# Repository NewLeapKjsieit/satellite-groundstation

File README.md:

# satellite-groundstation

Includes a arduino program to control ground station rotators

Componets->

1. esp8266 ( controller + wifi)	
	https://www.espressif.com/sites/default/files/documentation/0a-esp8266ex_datasheet_en.pdf
	-provide unregulted power supply to it
	-

2. drv8825 x 2(motor controller)-----
	https://www.pololu.com/product/2133
	https://lastminuteengineers.com/drv8825-stepper-motor-driver-arduino-tutorial/

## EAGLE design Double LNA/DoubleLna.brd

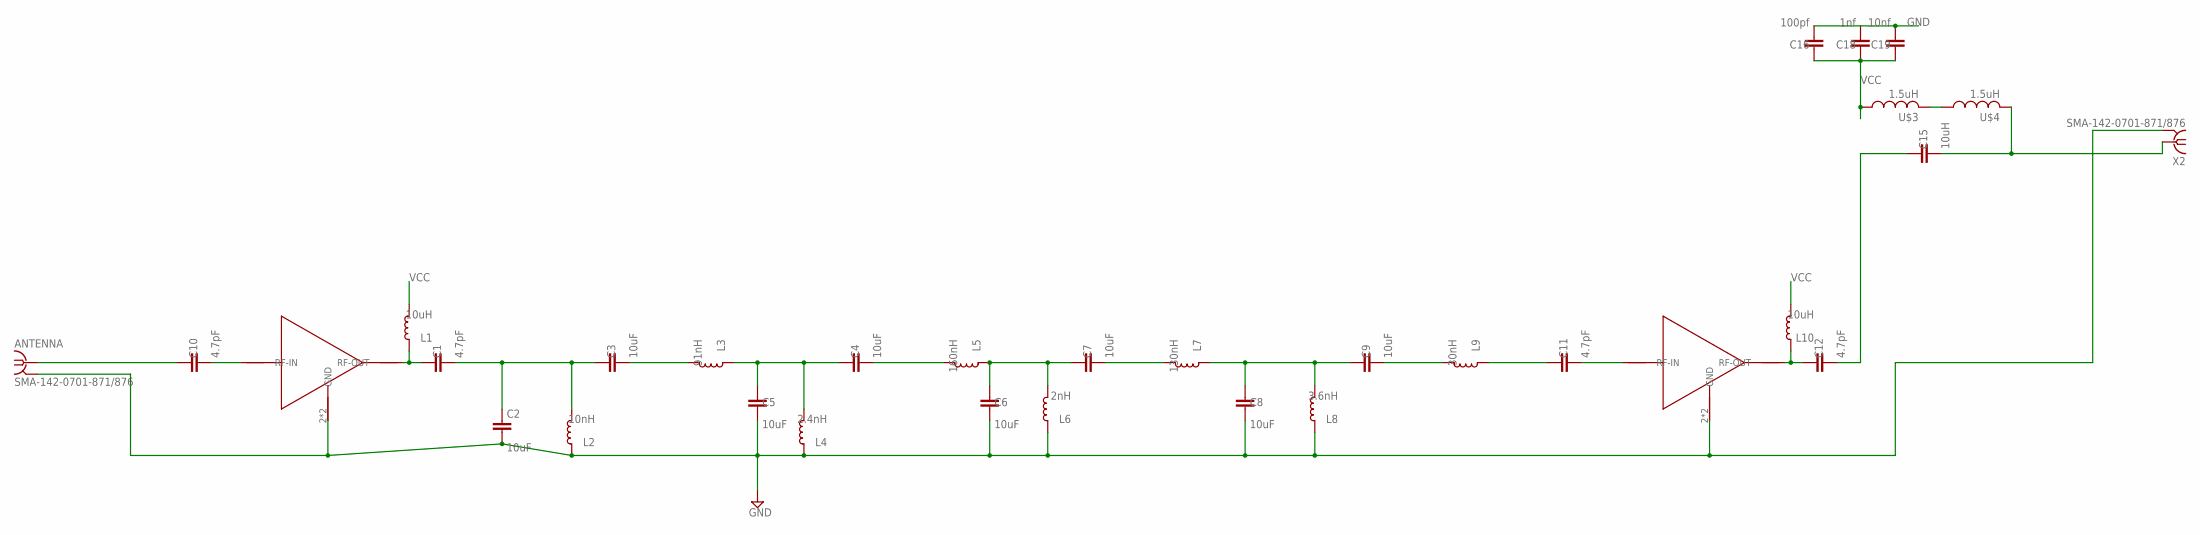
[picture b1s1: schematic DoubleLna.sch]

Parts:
ANTENNA: SMA-142-0701-871/876; J502-ND-142-0701-871/876
C1, C10, C11, C12: 4.7pF; 0603
C2, C3, C4, C5, C6, C7, C8, C9: 10uF; 0603
C15: 10uH; 0603
C16: 100pf; 0603
C18: 1nf; 0603
C19: 10nf; 0603
L1, L10: 10uH; L0603
L2: 10nH; L0603
L3: 91nH; L0603
L4: 2.4nH; L0603
L5: 160nH; L0603
L6: 2nH; L0603
L7: 130nH; L0603
L8: 3.6nH; L0603
L9: 30nH; L0603
U$1, U$2: PSA4-5043+
U$3, U$4: 1.5uH; C0504
X2: SMA-142-0701-871/876; J502-ND-142-0701-871/876

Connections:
GND: ANTENNA.G@1 (2), ANTENNA.G@2 (2), ANTENNA.G@3 (2), ANTENNA.G@4 (2), C2.2, C5.2, C6.2, C8.2, C16.2, C18.2, C19.2, L2.2, L4.2, L6.2, L8.2, U$1.2 (GND), U$1.4 (GND), U$2.2 (GND), U$2.4 (GND), X2.G@1 (2), X2.G@2 (2), X2.G@3 (2), X2.G@4 (2)
unnamed: ANTENNA.1, C10.1
unnamed: C1.2, C2.1, C3.1, L2.1
unnamed: C3.2, L3.1
unnamed: C4.1, C5.1, L3.2, L4.1
unnamed: C4.2, L5.1
unnamed: C6.1, C7.1, L5.2, L6.1
unnamed: C7.2, L7.1
unnamed: C8.1, C9.1, L7.2, L8.1
unnamed: C9.2, L9.1
unnamed: C10.2, U$1.3 (RF-IN)
unnamed: C1.1, L1.2, U$1.1 (RF-OUT)
unnamed: C12.1, L10.2, U$2.1 (RF-OUT)
unnamed: C11.2, U$2.3 (RF-IN)
unnamed: C12.2, C15.1
unnamed: C11.1, L9.2
unnamed: C15.2, U$4.2, X2.1
unnamed: U$3.2, U$4.1
VCC: C16.1, C18.1, C19.1, L1.1, L10.1, U$3.1

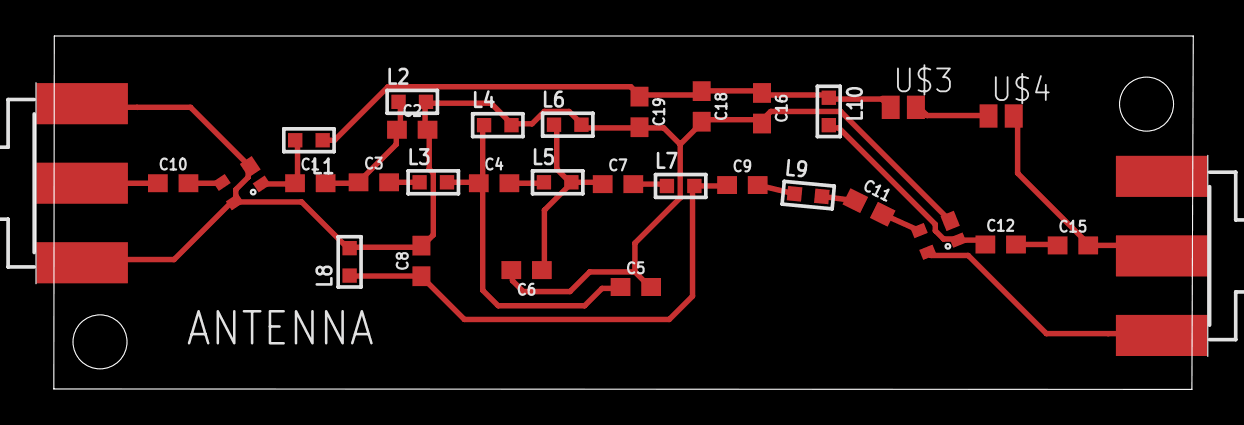
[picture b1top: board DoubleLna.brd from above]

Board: 2 copper layers, 65.1 x 19.6 mm, 32 parts (0 on the bottom side), 19 nets.

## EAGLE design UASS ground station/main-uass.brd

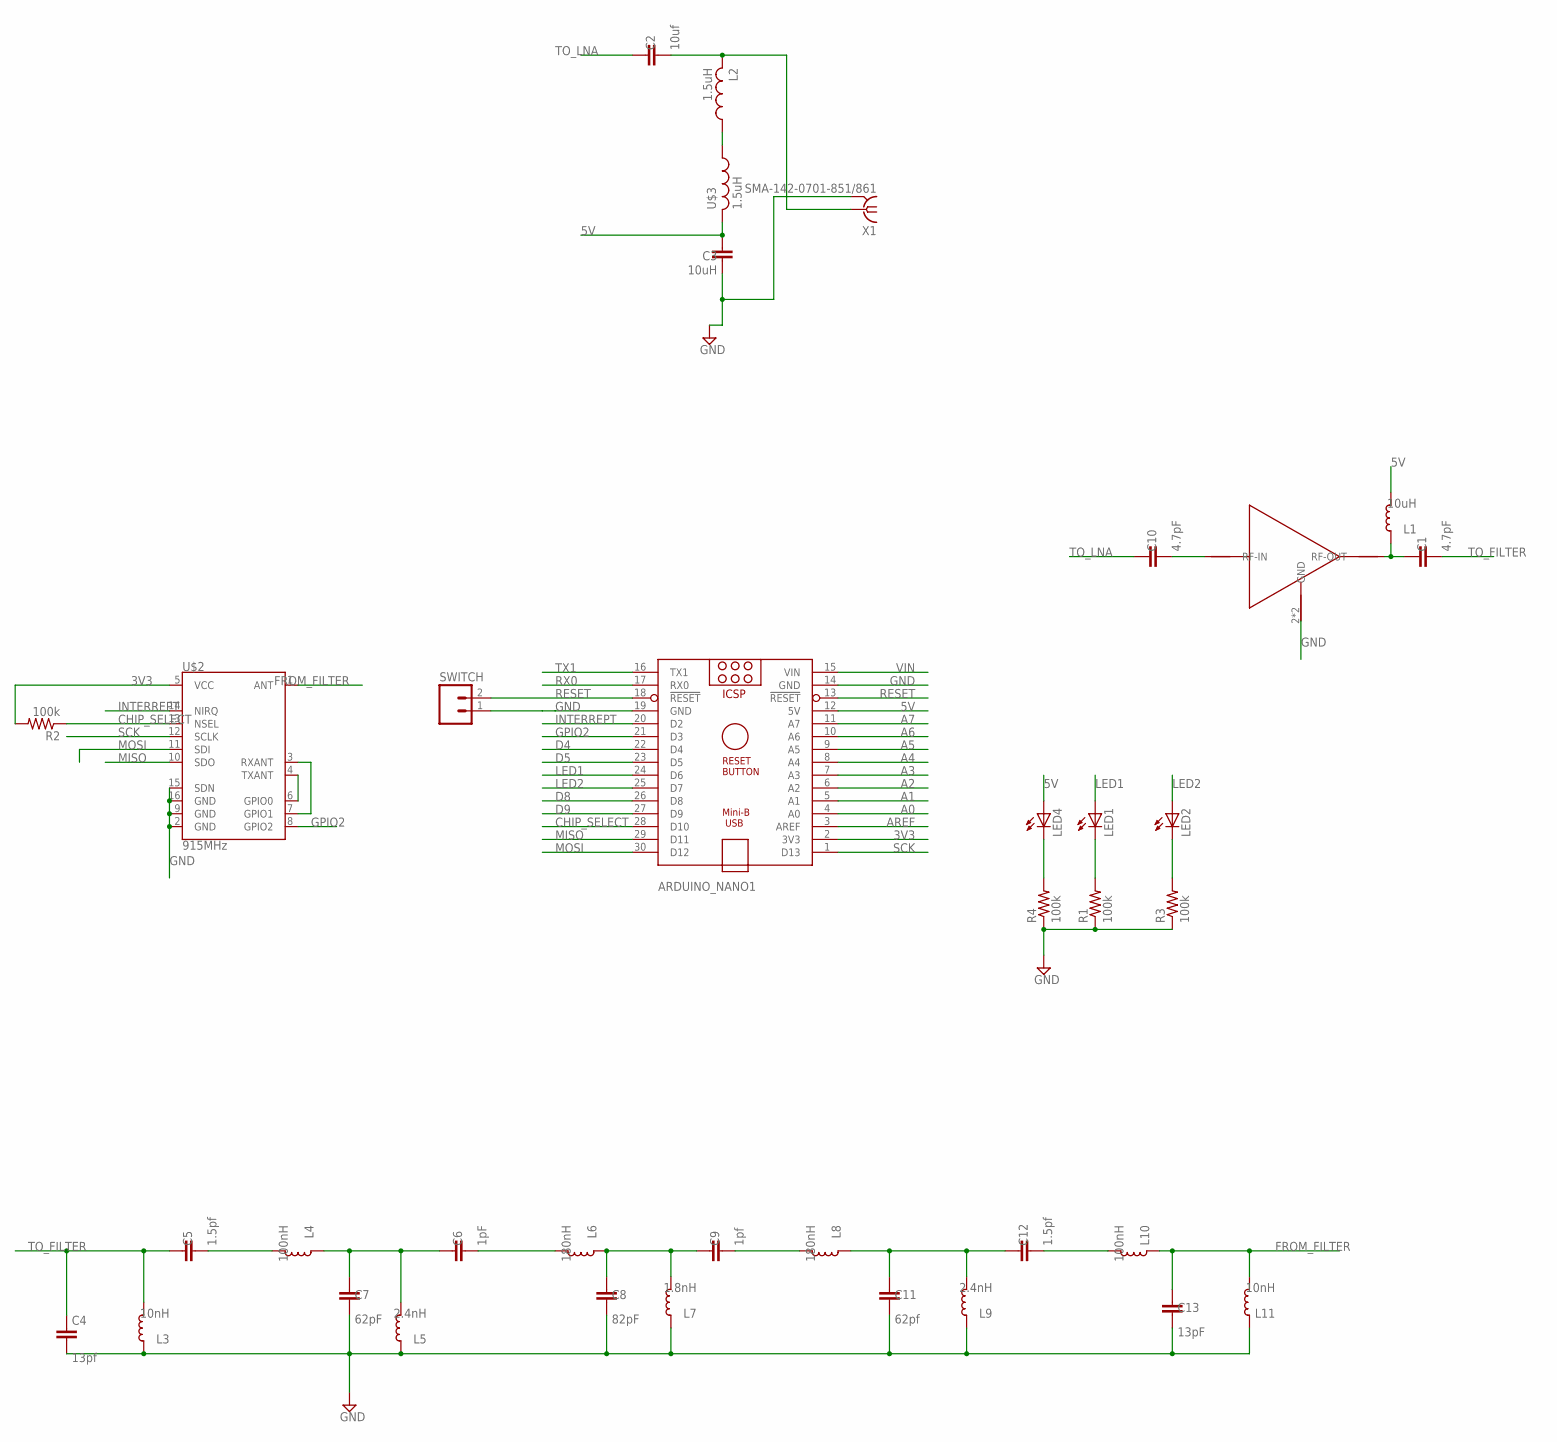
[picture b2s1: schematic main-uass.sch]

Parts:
ARDUINO_NANO1: ARDUINO_NANO
C1, C10: 4.7pF; 0603
C2: 10uf; 0603
C3: 10uH; 0603
C4: 13pf; 0603
C5, C12: 1.5pf; 0603
C6: 1pF; 0603
C7: 62pF; 0603
C8: 82pF; 0603
C9: 1pf; 0603
C11: 62pf; 0603
C13: 13pF; 0603
L1: 10uH; L0603
L2: 1.5uH; C0504
L3, L11: 10nH; L0603
L4, L10: 100nH; L0603
L5, L9: 2.4nH; L0603
L6, L8: 180nH; L0603
L7: 1.8nH; L0603
LED1, LED2, LED4: LED5MM
R1, R2, R3, R4: 100k; R0603
SWITCH: M02; 02P
U$1: PSA4-5043+
U$2: 915MHz; RFM22-XXX-S2
U$3: 1.5uH; C0504
X1: SMA-142-0701-851/861; J502-ND-142-0701-851/861

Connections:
3V3: ARDUINO_NANO1.2 (3V3), R2.2, U$2.5 (VCC)
5V: ARDUINO_NANO1.12 (5V), C3.2, L1.1, LED4.A, U$3.2
A0: ARDUINO_NANO1.4 (A0)
A1: ARDUINO_NANO1.5 (A1)
A2: ARDUINO_NANO1.6 (A2)
A3: ARDUINO_NANO1.7 (A3)
A4: ARDUINO_NANO1.8 (A4)
A5: ARDUINO_NANO1.9 (A5)
A6: ARDUINO_NANO1.10 (A6)
A7: ARDUINO_NANO1.11 (A7)
AREF: ARDUINO_NANO1.3 (AREF)
CHIP_SELECT: ARDUINO_NANO1.28 (D10), R2.1, U$2.13 (NSEL)
D4: ARDUINO_NANO1.22 (D4)
D5: ARDUINO_NANO1.23 (D5)
D8: ARDUINO_NANO1.26 (D8)
D9: ARDUINO_NANO1.27 (D9)
FROM_FILTER: C13.1, L10.2, L11.1, U$2.1 (ANT)
GND: ARDUINO_NANO1.14 (GND), ARDUINO_NANO1.19 (GND), C3.1, C4.2, C7.2, C8.2, C11.2, C13.2, L3.2, L5.2, L7.2, L9.2, L11.2, R1.1, R3.1, R4.1, SWITCH.1, U$1.2 (GND), U$1.4 (GND), U$2.2 (GND), U$2.9 (GND), U$2.15 (SDN), U$2.16 (GND), X1.G@1 (2), X1.G@2 (2), X1.G@3 (2), X1.G@4 (2)
GPIO2: ARDUINO_NANO1.21 (D3), U$2.8 (GPIO2)
INTERREPT: ARDUINO_NANO1.20 (D2), U$2.14 (NIRQ)
LED1: ARDUINO_NANO1.24 (D6), LED1.A
LED2: ARDUINO_NANO1.25 (D7), LED2.A
MISO: ARDUINO_NANO1.29 (D11), U$2.10 (SDO)
MOSI: ARDUINO_NANO1.30 (D12), U$2.11 (SDI)
unnamed: U$2.4 (TXANT), U$2.6 (GPIO0)
unnamed: U$2.3 (RXANT), U$2.7 (GPIO1)
unnamed: L2.1, U$3.1
unnamed: C5.2, L4.1
unnamed: C6.1, C7.1, L4.2, L5.1
unnamed: C6.2, L6.1
unnamed: C8.1, C9.1, L6.2, L7.1
unnamed: C9.2, L8.1
unnamed: C11.1, C12.1, L8.2, L9.1
unnamed: C12.2, L10.1
unnamed: LED2.K (C), R3.2
unnamed: LED4.K (C), R4.2
unnamed: LED1.K (C), R1.2
unnamed: C10.2, U$1.3 (RF-IN)
unnamed: C1.1, L1.2, U$1.1 (RF-OUT)
unnamed: C2.2, L2.2, X1.1
RESET: ARDUINO_NANO1.13 (!RESET), ARDUINO_NANO1.18 (!RESET), SWITCH.2
RX0: ARDUINO_NANO1.17 (RX0)
SCK: ARDUINO_NANO1.1 (D13), U$2.12 (SCLK)
TO_FILTER: C1.2, C4.1, C5.1, L3.1
TO_LNA: C2.1, C10.1
TX1: ARDUINO_NANO1.16 (TX1)
VIN: ARDUINO_NANO1.15 (VIN)

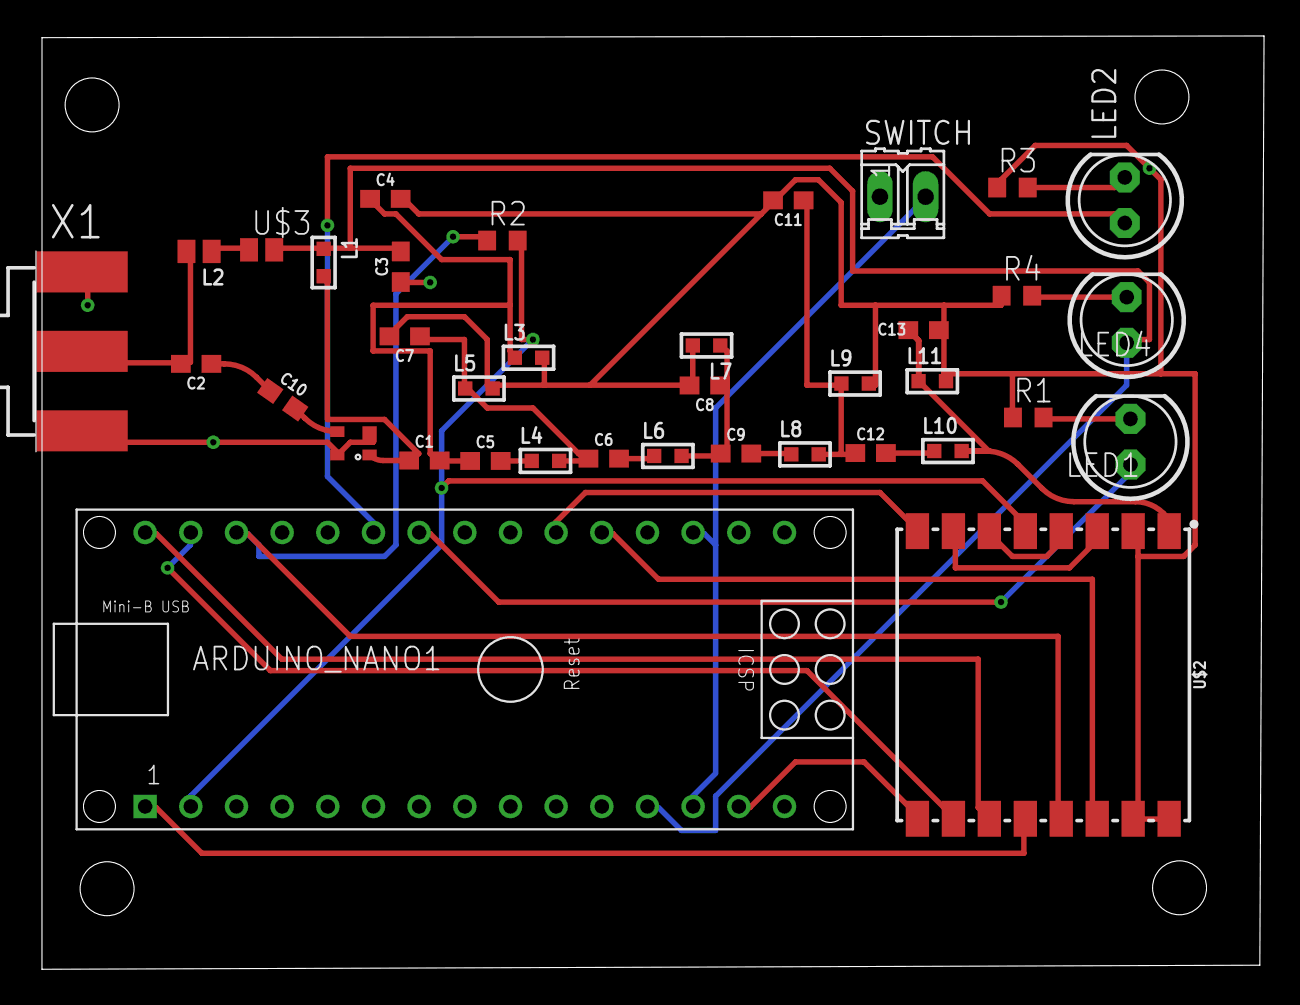
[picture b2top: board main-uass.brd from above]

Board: 2 copper layers, 68.0 x 51.9 mm, 37 parts (0 on the bottom side), 31 nets.

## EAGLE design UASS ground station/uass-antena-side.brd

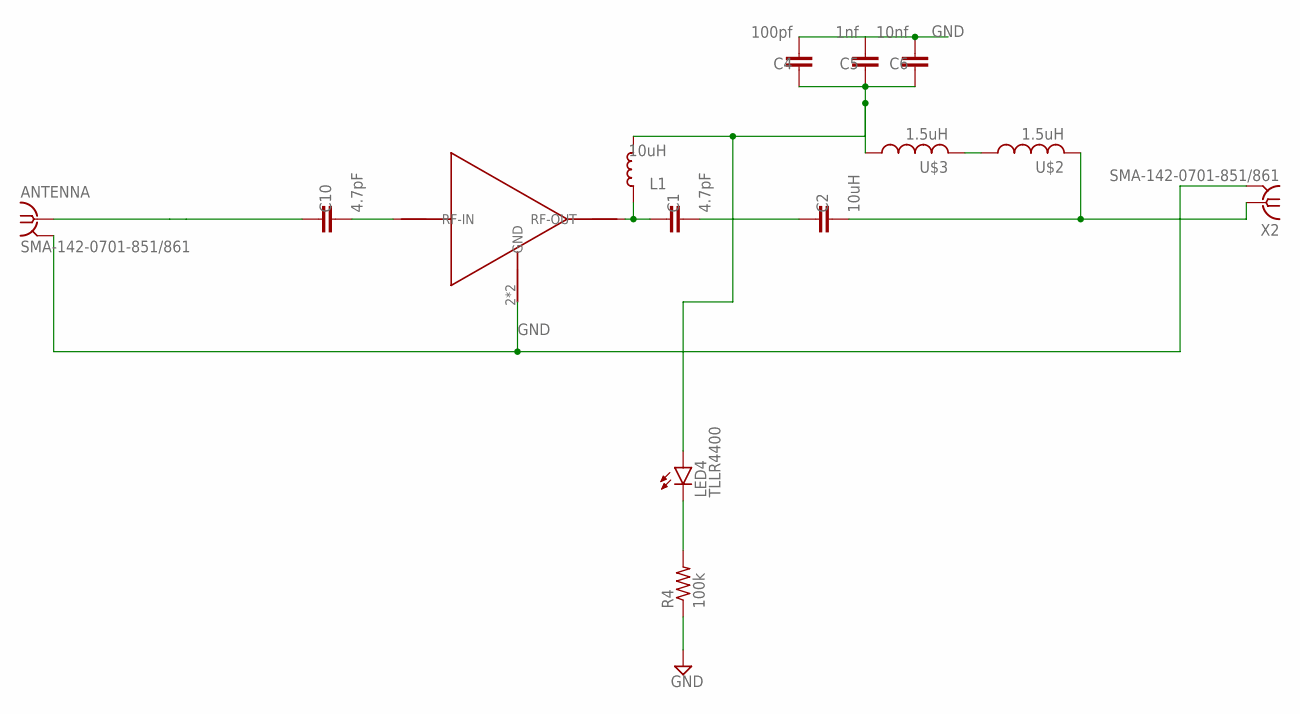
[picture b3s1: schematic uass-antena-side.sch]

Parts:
ANTENNA: SMA-142-0701-851/861; J502-ND-142-0701-851/861
C1, C10: 4.7pF; 0603
C2: 10uH; 0603
C4: 100pf; 0603
C5: 1nf; 0603
C6: 10nf; 0603
L1: 10uH; L0603
LED4: TLLR4400; LED3MM
R4: 100k; R0603
U$1: PSA4-5043+
U$2, U$3: 1.5uH; C0504
X2: SMA-142-0701-851/861; J502-ND-142-0701-851/861

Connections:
5V: C4.1, C5.1, C6.1, L1.1, LED4.A, U$3.1
GND: ANTENNA.G@1 (2), ANTENNA.G@2 (2), ANTENNA.G@3 (2), ANTENNA.G@4 (2), C4.2, C5.2, C6.2, R4.1, U$1.2 (GND), U$1.4 (GND), X2.G@1 (2), X2.G@2 (2), X2.G@3 (2), X2.G@4 (2)
unnamed: C2.2, U$2.2, X2.1
unnamed: U$2.1, U$3.2
unnamed: C1.2, C2.1
unnamed: LED4.K (C), R4.2
unnamed: ANTENNA.1, C10.1
unnamed: C10.2, U$1.3 (RF-IN)
unnamed: C1.1, L1.2, U$1.1 (RF-OUT)

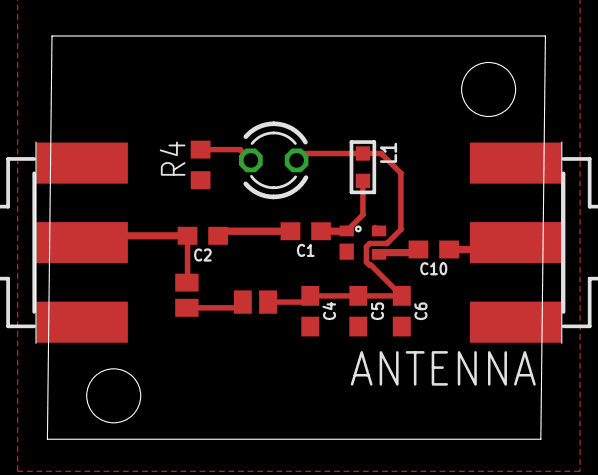
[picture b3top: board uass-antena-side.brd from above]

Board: 2 copper layers, 29.2 x 22.4 mm, 14 parts (0 on the bottom side), 9 nets.

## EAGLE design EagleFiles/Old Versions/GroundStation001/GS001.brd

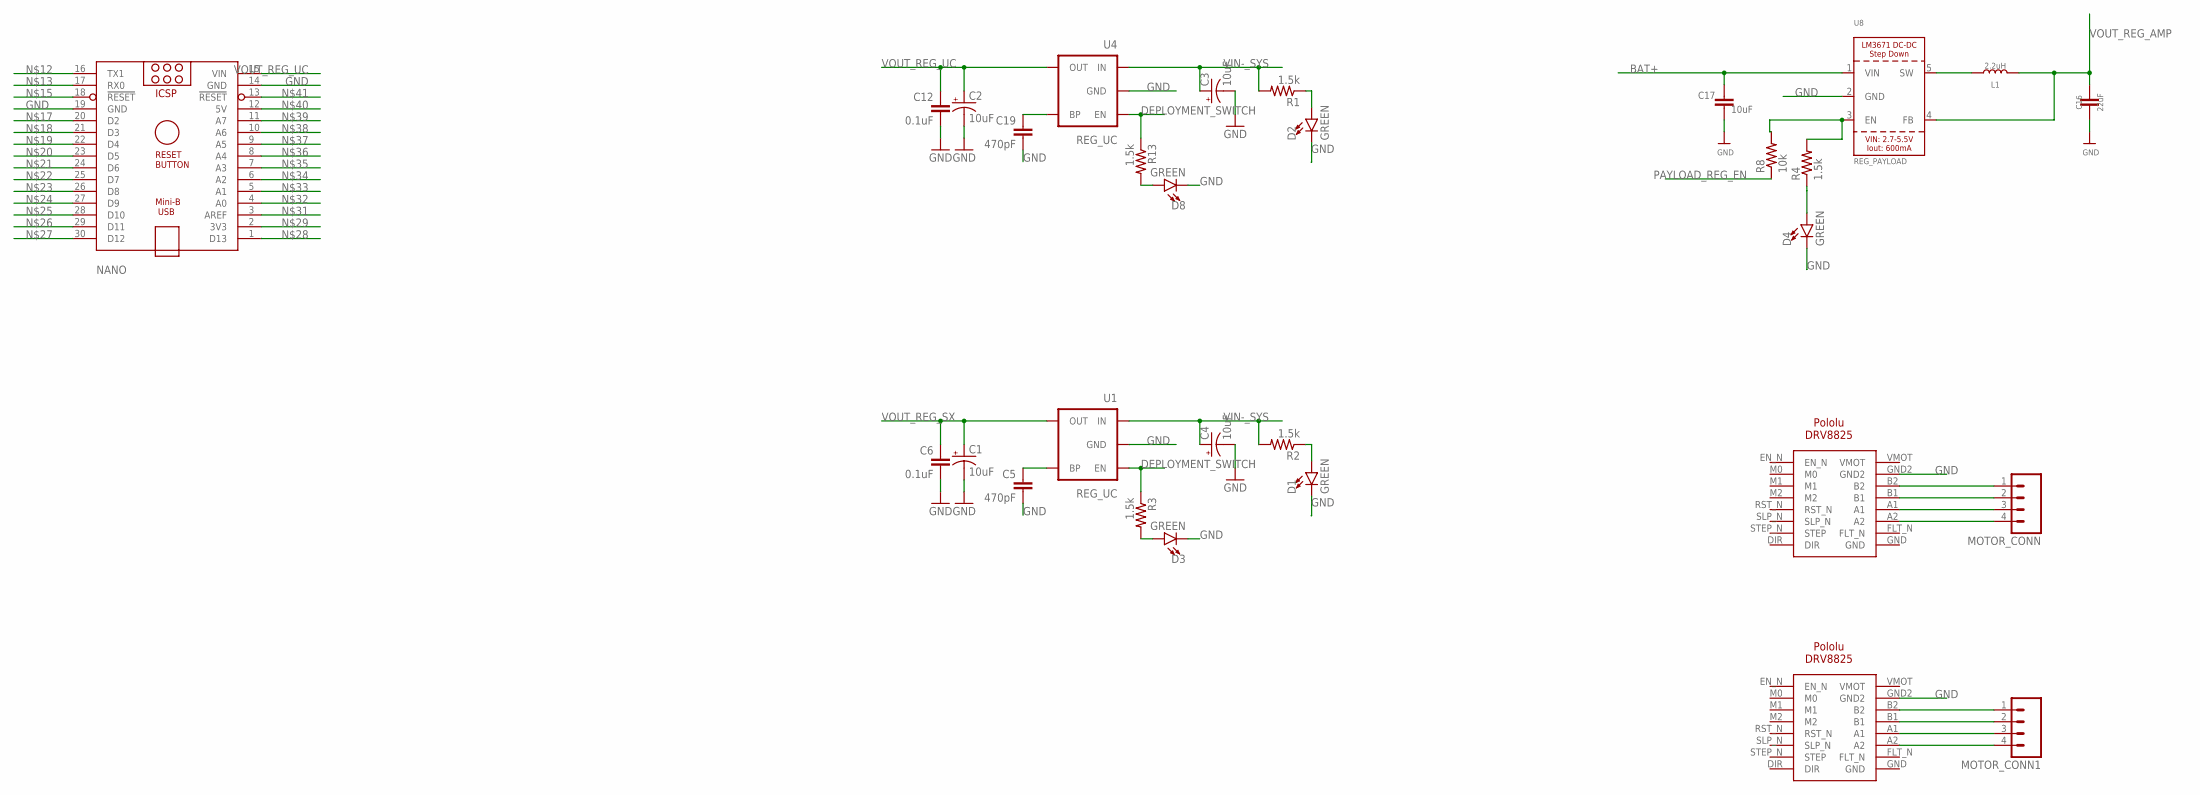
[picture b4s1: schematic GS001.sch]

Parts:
C1, C2, C3, C4: 10uF; 0603-POLAR
C5, C19: 470pF; 0603-CAP
C6, C12: 0.1uF; 0603-CAP
C16: 22uF; 0603
C17: 10uF; 0603
D1, D2, D3, D4, D8: GREEN; LED-0603
L1: 2.2uH; 0603
MOTOR_CONN, MOTOR_CONN1: M04; 04P
NANO: ARDUINO_NANO
R1, R2, R3, R4, R13: 1.5k; 0603-RES
R8: 10k; 0402-RES
U1, U4: REG_UC; SOT23-5
U8: REG_PAYLOAD; SOT23-5
U$1, U$4: POLOLU-DRV8825

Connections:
BAT+: C17.1, U8.1 (VIN)
DEPLOYMENT_SWITCH: R3.1, R13.1, U1.3 (EN), U4.3 (EN)
GND: C1.-, C2.-, C3.-, C4.-, C5.2, C6.2, C12.2, C16.2, C17.2, C19.2, D1.C, D2.C, D3.C, D4.C, D8.C, NANO.14 (GND), NANO.19 (GND), U1.2 (GND), U4.2 (GND), U8.2 (GND), U$1.GND2, U$4.GND2
unnamed: C5.1, U1.4 (BP)
unnamed: D8.A, R13.2
unnamed: D3.A, R3.2
unnamed: D1.A, R2.1
unnamed: MOTOR_CONN.1, U$1.B2
unnamed: D4.A, R4.1
unnamed: D2.A, R1.1
unnamed: MOTOR_CONN.2, U$1.B1
unnamed: R4.2, R8.2, U8.3 (EN)
unnamed: MOTOR_CONN.3, U$1.A1
unnamed: MOTOR_CONN.4, U$1.A2
unnamed: L1.1, U8.5 (SW)
unnamed: MOTOR_CONN1.1, U$4.B2
unnamed: C19.1, U4.4 (BP)
unnamed: MOTOR_CONN1.2, U$4.B1
unnamed: MOTOR_CONN1.3, U$4.A1
unnamed: MOTOR_CONN1.4, U$4.A2
PAYLOAD_REG_EN: R8.1
VIN-_SYS: C3.+, C4.+, R1.2, R2.2, U1.1 (IN), U4.1 (IN)
VOUT_REG_AMP: C16.1, L1.2, U8.4 (FB)
VOUT_REG_SX: C1.+, C6.1, U1.5 (OUT)
VOUT_REG_UC: C2.+, C12.1, NANO.15 (VIN), U4.5 (OUT)

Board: 2 copper layers, 30 parts (0 on the bottom side), 24 nets, no tracks yet.

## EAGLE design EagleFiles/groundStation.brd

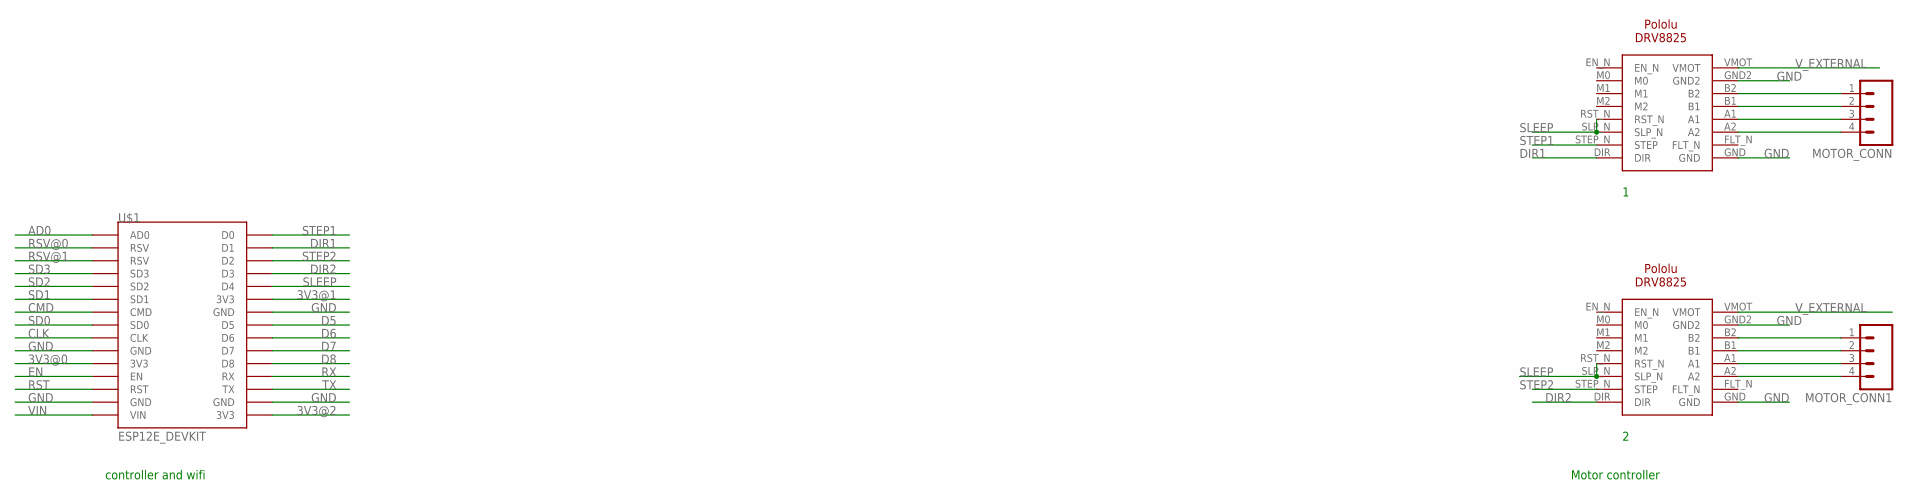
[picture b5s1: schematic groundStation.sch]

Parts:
MOTOR_CONN, MOTOR_CONN1: M04; 04P
U$1: ESP12E_DEVKIT
U$2, U$4: POLOLU-DRV8825

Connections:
3V3@0: U$1.3V3@0 (3V3)
3V3@1: U$1.3V3@1 (3V3)
3V3@2: U$1.3V3@2 (3V3)
AD0: U$1.AD0
CLK: U$1.CLK
CMD: U$1.CMD
D5: U$1.D5
D6: U$1.D6
D7: U$1.D7
D8: U$1.D8
DIR1: U$1.D1, U$2.DIR
DIR2: U$1.D3, U$4.DIR
EN: U$1.EN
GND: U$1.GND@0 (GND), U$1.GND@1 (GND), U$1.GND@2 (GND), U$1.GND@3 (GND), U$2.GND, U$2.GND2, U$4.GND, U$4.GND2
unnamed: MOTOR_CONN.1, U$2.B2
unnamed: MOTOR_CONN.2, U$2.B1
unnamed: MOTOR_CONN.3, U$2.A1
unnamed: MOTOR_CONN.4, U$2.A2
unnamed: MOTOR_CONN1.1, U$4.B2
unnamed: MOTOR_CONN1.2, U$4.B1
unnamed: MOTOR_CONN1.3, U$4.A1
unnamed: MOTOR_CONN1.4, U$4.A2
RST: U$1.RST
RSV@0: U$1.RSV@0 (RSV)
RSV@1: U$1.RSV@1 (RSV)
RX: U$1.RX
SD0: U$1.SD0
SD1: U$1.SD1
SD2: U$1.SD2
SD3: U$1.SD3
SLEEP: U$1.D4, U$2.RST_N, U$2.SLP_N, U$4.RST_N, U$4.SLP_N
STEP1: U$1.D0, U$2.STEP_N (STEP)
STEP2: U$1.D2, U$4.STEP_N (STEP)
TX: U$1.TX
VIN: U$1.VIN
V_EXTERNAL: U$2.VMOT, U$4.VMOT

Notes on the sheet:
Motor controller
controller and wifi

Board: 2 copper layers, 5 parts (0 on the bottom side), 15 nets, no tracks yet.

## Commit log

2019-03-18 The alpha version
2019-07-03 corrected errors and impprovised
2020-06-03 basic setups
2020-06-03 added few components
2020-06-11 motor controller done
2020-06-11 small changes in motor control
2020-07-04 rfffm6406 library done
2020-07-04 added basic circuit for rffm tp4056
2020-07-04 added img for diect view
2020-07-09 added the basic battery circuit
2020-07-09 removed image
2020-07-15 added double LNA to project v.01
2020-07-21 added uass ground station

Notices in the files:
parts and their libraries:
SparkFun-Capacitors: Licensing: Creative Commons ShareAlike 4.0 International - https://creativecommons.org/licenses/by-sa/4.0
rc-master-smd: Copyright (C) 2007, Bob Starr
